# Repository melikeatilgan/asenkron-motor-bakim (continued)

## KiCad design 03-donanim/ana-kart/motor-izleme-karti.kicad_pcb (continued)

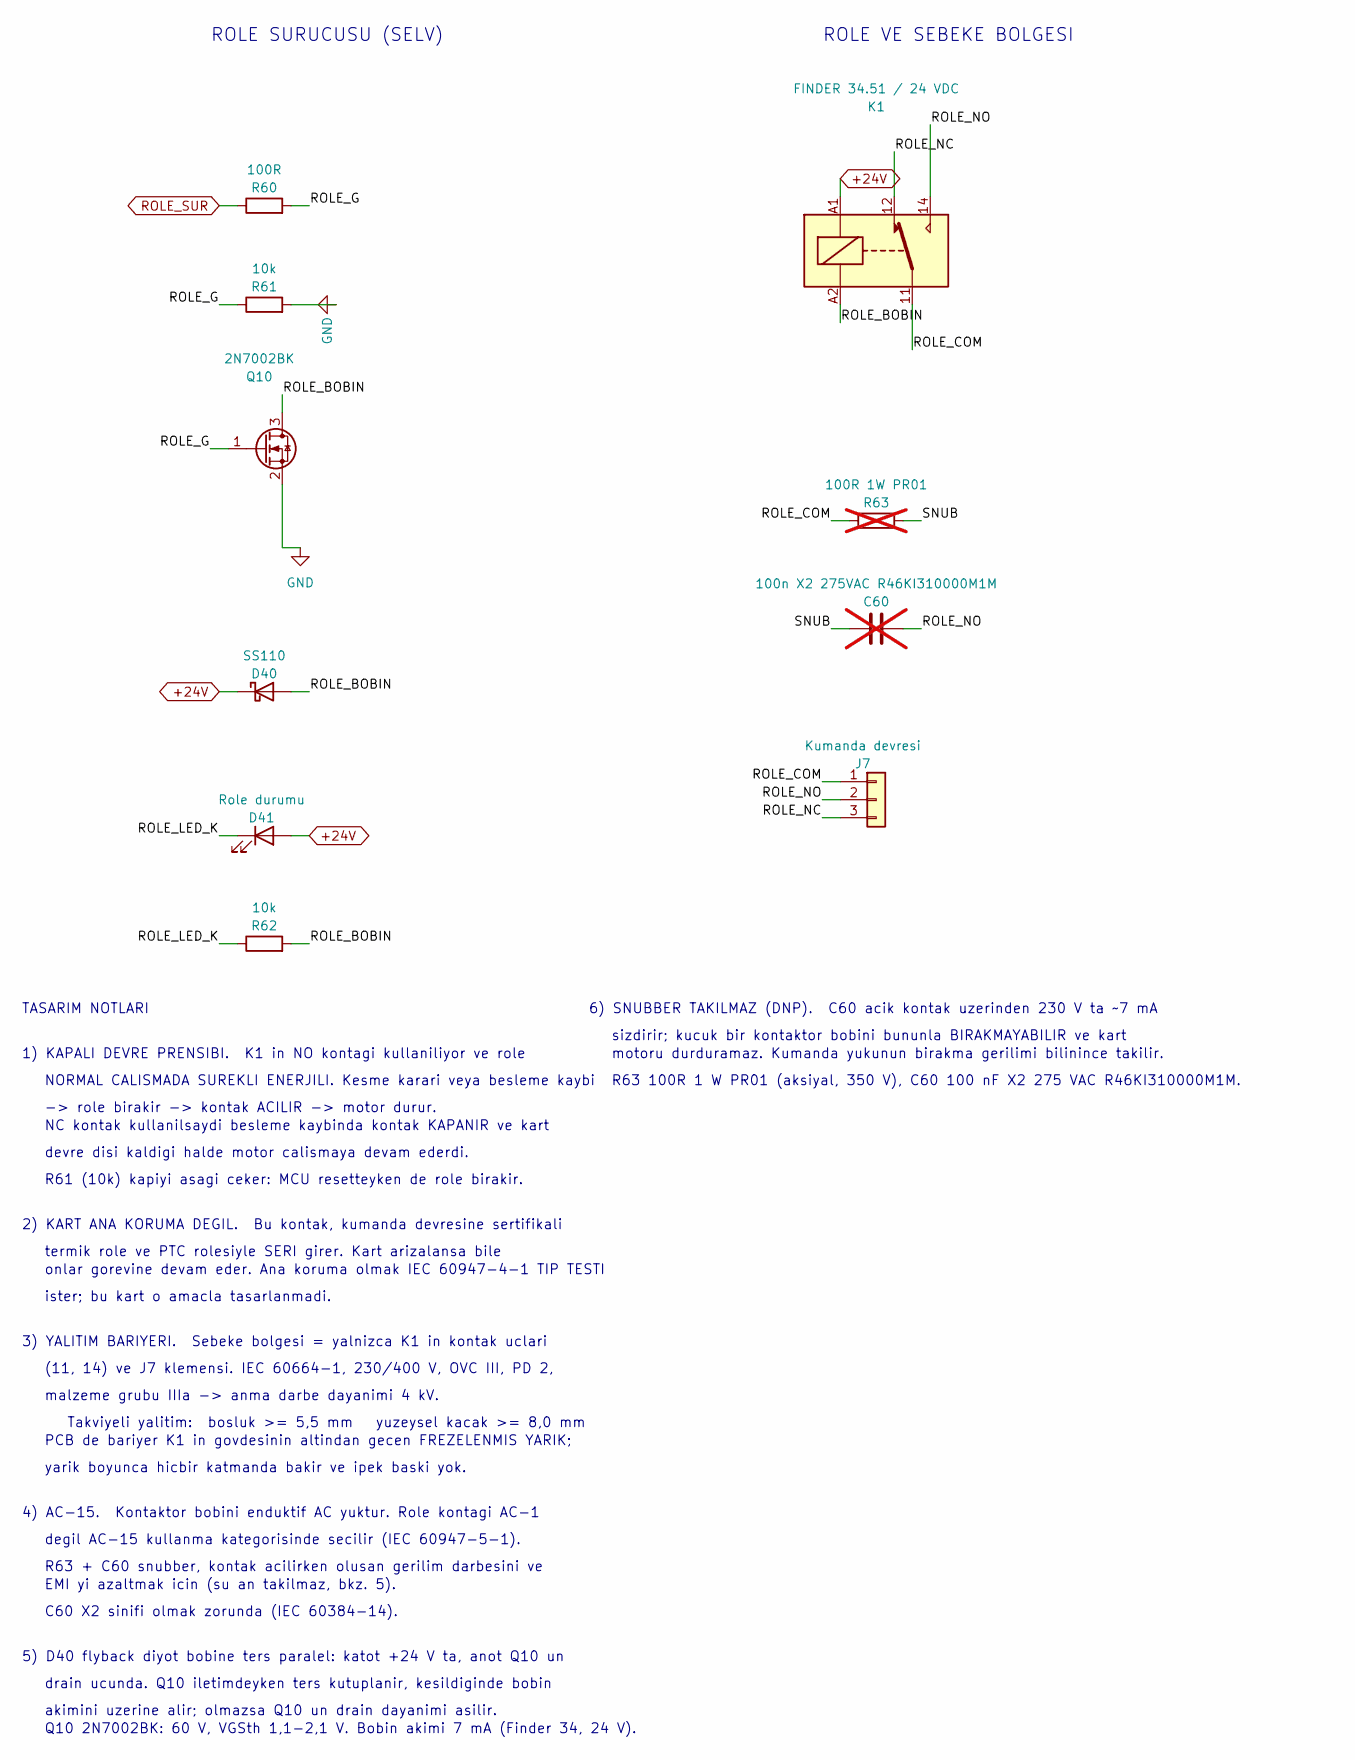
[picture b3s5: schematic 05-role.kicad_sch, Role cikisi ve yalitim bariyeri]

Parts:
C60: 100n X2 275VAC R46KI310000M1M; C_Rect_L18.0mm_W6.0mm_P15.00mm_FKS3_FKP3; not fitted
D40: SS110; D_SMA
D41: Role durumu; LED_0805_2012Metric
J7: Kumanda devresi; TerminalBlock_Phoenix_MKDS-1,5-3_1x03_P5.00mm_Horizontal
K1: FINDER 34.51 / 24 VDC; Relay_SPDT_Finder_34.51_Vertical_Fab
Q10: 2N7002BK; SOT-23
R60: 100R; R_0805_2012Metric
R61, R62: 10k; R_0805_2012Metric
R63: 100R 1W PR01; R_Axial_DIN0207_L6.3mm_D2.5mm_P10.16mm_Horizontal; not fitted

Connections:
+24V: D40.1 (K), D41.2 (A), K1.A1; also elsewhere on the board
/05-role/ROLE_BOBIN: D40.2 (A), K1.A2, Q10.3 (D), R62.2
/05-role/ROLE_COM: J7.1, K1.11, R63.1
/05-role/ROLE_G: Q10.1 (G), R60.2, R61.1
/05-role/ROLE_LED_K: D41.1 (K), R62.1
/05-role/ROLE_NC: J7.3, K1.12
/05-role/ROLE_NO: C60.2, J7.2, K1.14
/05-role/SNUB: C60.1, R63.2
GND: Q10.2 (S), R61.2; also elsewhere on the board
ROLE_SUR: R60.1; also elsewhere on the board

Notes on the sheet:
Q10 2N7002BK: 60 V, VGSth 1,1-2,1 V. Bobin akimi 7 mA (Finder 34, 24 V).
motoru durduramaz. Kumanda yukunun birakma gerilimi bilinince takilir.
Takviyeli yalitim: bosluk >= 5,5 mm yuzeysel kacak >= 8,0 mm
NORMAL CALISMADA SUREKLI ENERJILI. Kesme karari veya besleme kaybi
5) D40 flyback diyot bobine ters paralel: katot +24 V ta, anot Q10 un
devre disi kaldigi halde motor calismaya devam ederdi.
termik role ve PTC rolesiyle SERI girer. Kart arizalansa bile
6) SNUBBER TAKILMAZ (DNP). C60 acik kontak uzerinden 230 V ta ~7 mA
3) YALITIM BARIYERI. Sebeke bolgesi = yalnizca K1 in kontak uclari
degil AC-15 kullanma kategorisinde secilir (IEC 60947-5-1).
EMI yi azaltmak icin (su an takilmaz, bkz. 5).
1) KAPALI DEVRE PRENSIBI. K1 in NO kontagi kullaniliyor ve role
akimini uzerine alir; olmazsa Q10 un drain dayanimi asilir.
2) KART ANA KORUMA DEGIL. Bu kontak, kumanda devresine sertifikali
R61 (10k) kapiyi asagi ceker: MCU resetteyken de role birakir.
NC kontak kullanilsaydi besleme kaybinda kontak KAPANIR ve kart
onlar gorevine devam eder. Ana koruma olmak IEC 60947-4-1 TIP TESTI
ister; bu kart o amacla tasarlanmadi.
(11, 14) ve J7 klemensi. IEC 60664-1, 230/400 V, OVC III, PD 2,
R63 + C60 snubber, kontak acilirken olusan gerilim darbesini ve
yarik boyunca hicbir katmanda bakir ve ipek baski yok.
sizdirir; kucuk bir kontaktor bobini bununla BIRAKMAYABILIR ve kart
ROLE SURUCUSU (SELV)
TASARIM NOTLARI
R63 100R 1 W PR01 (aksiyal, 350 V), C60 100 nF X2 275 VAC R46KI310000M1M.
4) AC-15. Kontaktor bobini enduktif AC yuktur. Role kontagi AC-1
ROLE VE SEBEKE BOLGESI
drain ucunda. Q10 iletimdeyken ters kutuplanir, kesildiginde bobin
PCB de bariyer K1 in govdesinin altindan gecen FREZELENMIS YARIK;
malzeme grubu IIIa -> anma darbe dayanimi 4 kV.
-> role birakir -> kontak ACILIR -> motor durur.
C60 X2 sinifi olmak zorunda (IEC 60384-14).

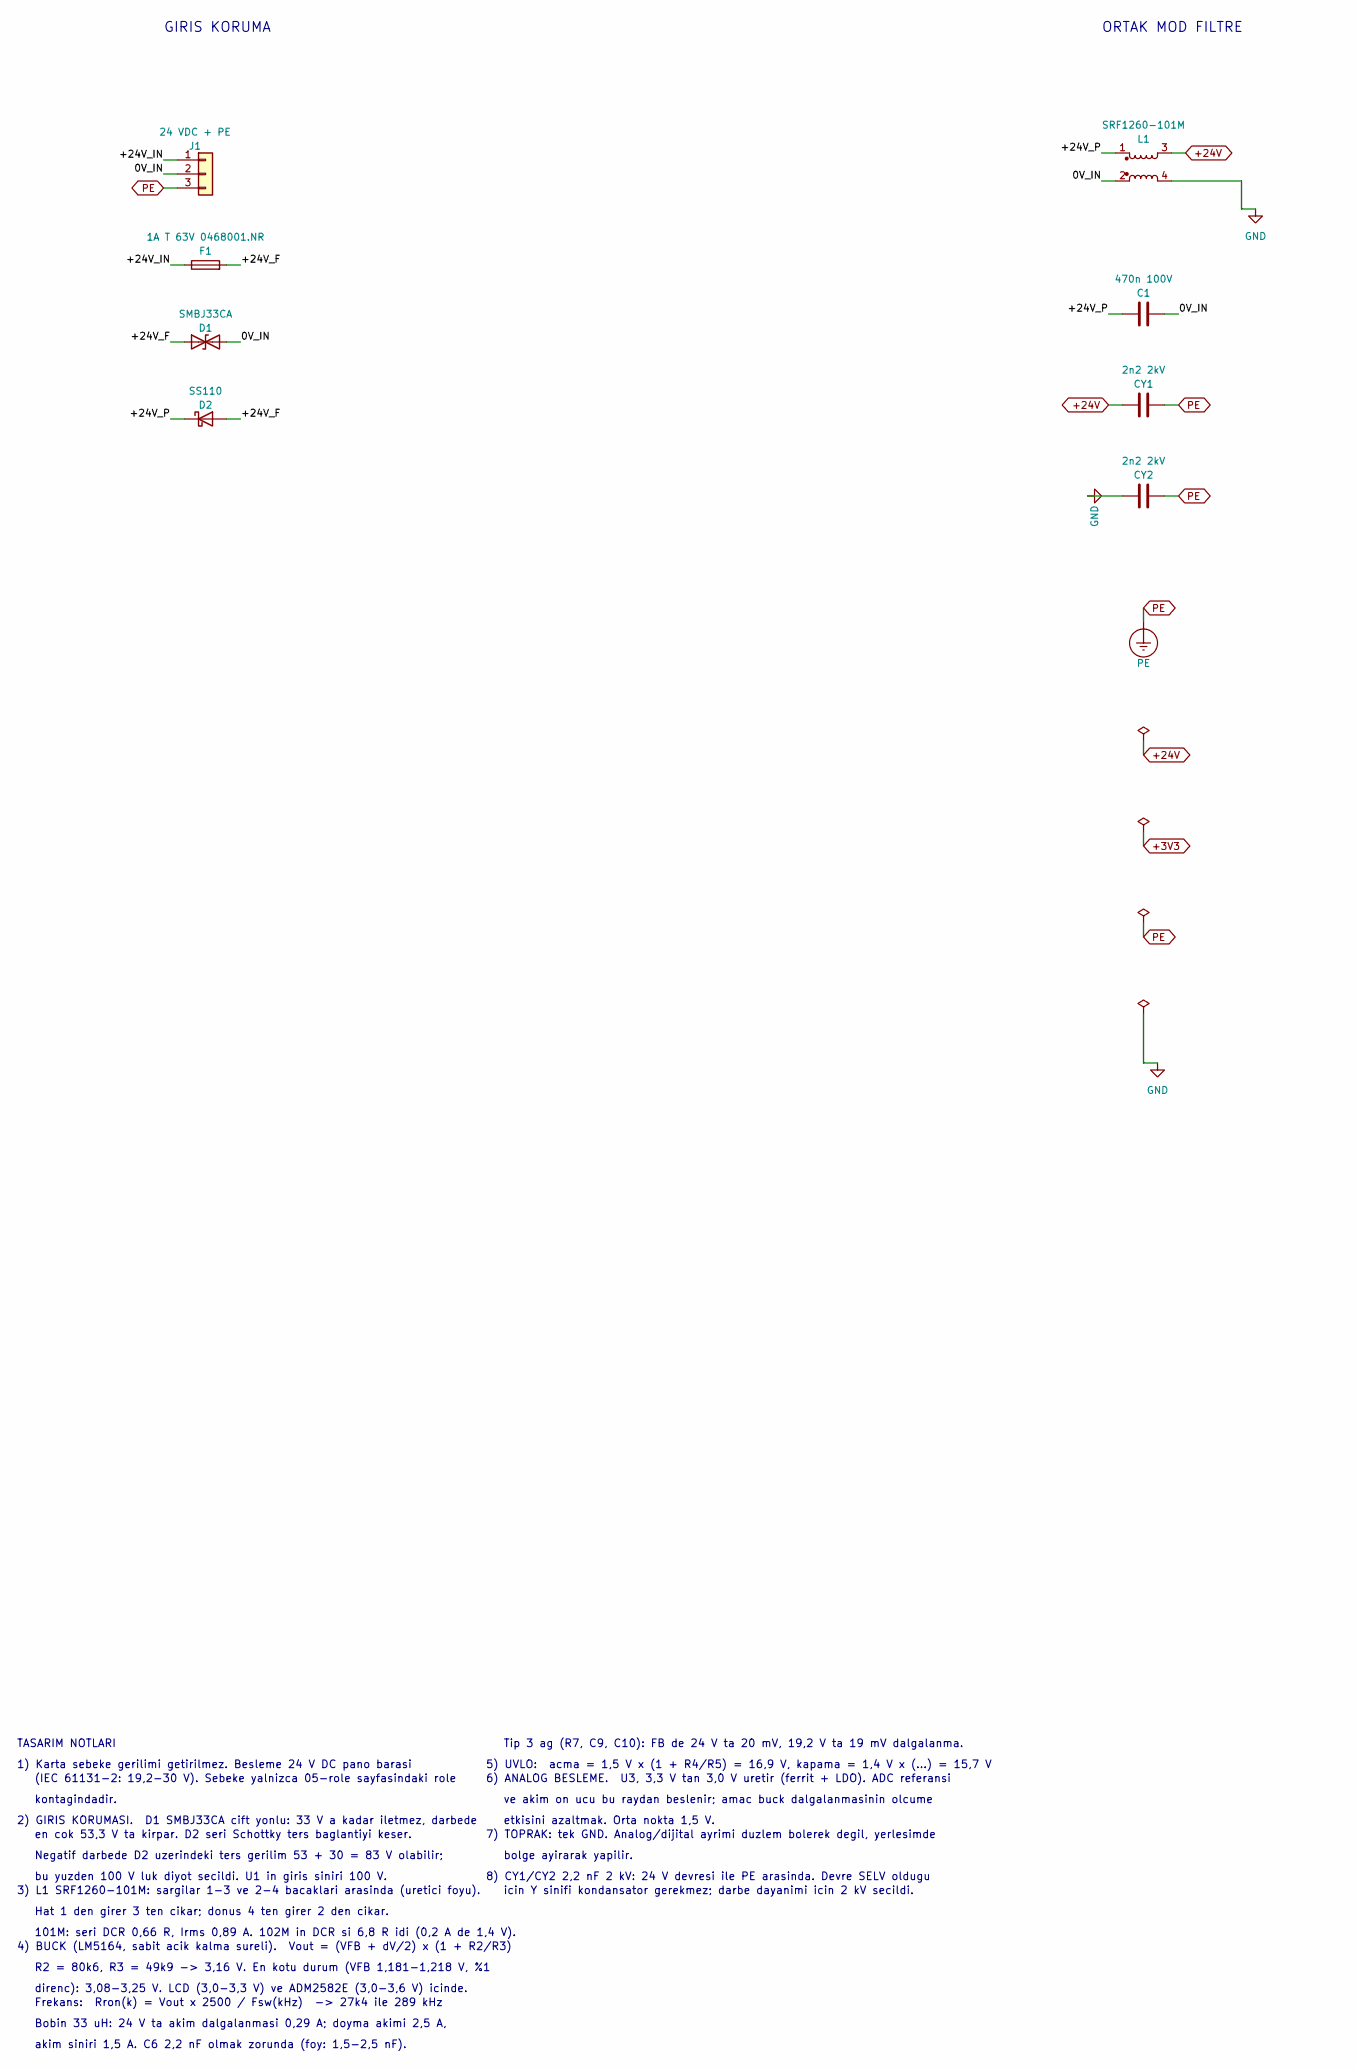
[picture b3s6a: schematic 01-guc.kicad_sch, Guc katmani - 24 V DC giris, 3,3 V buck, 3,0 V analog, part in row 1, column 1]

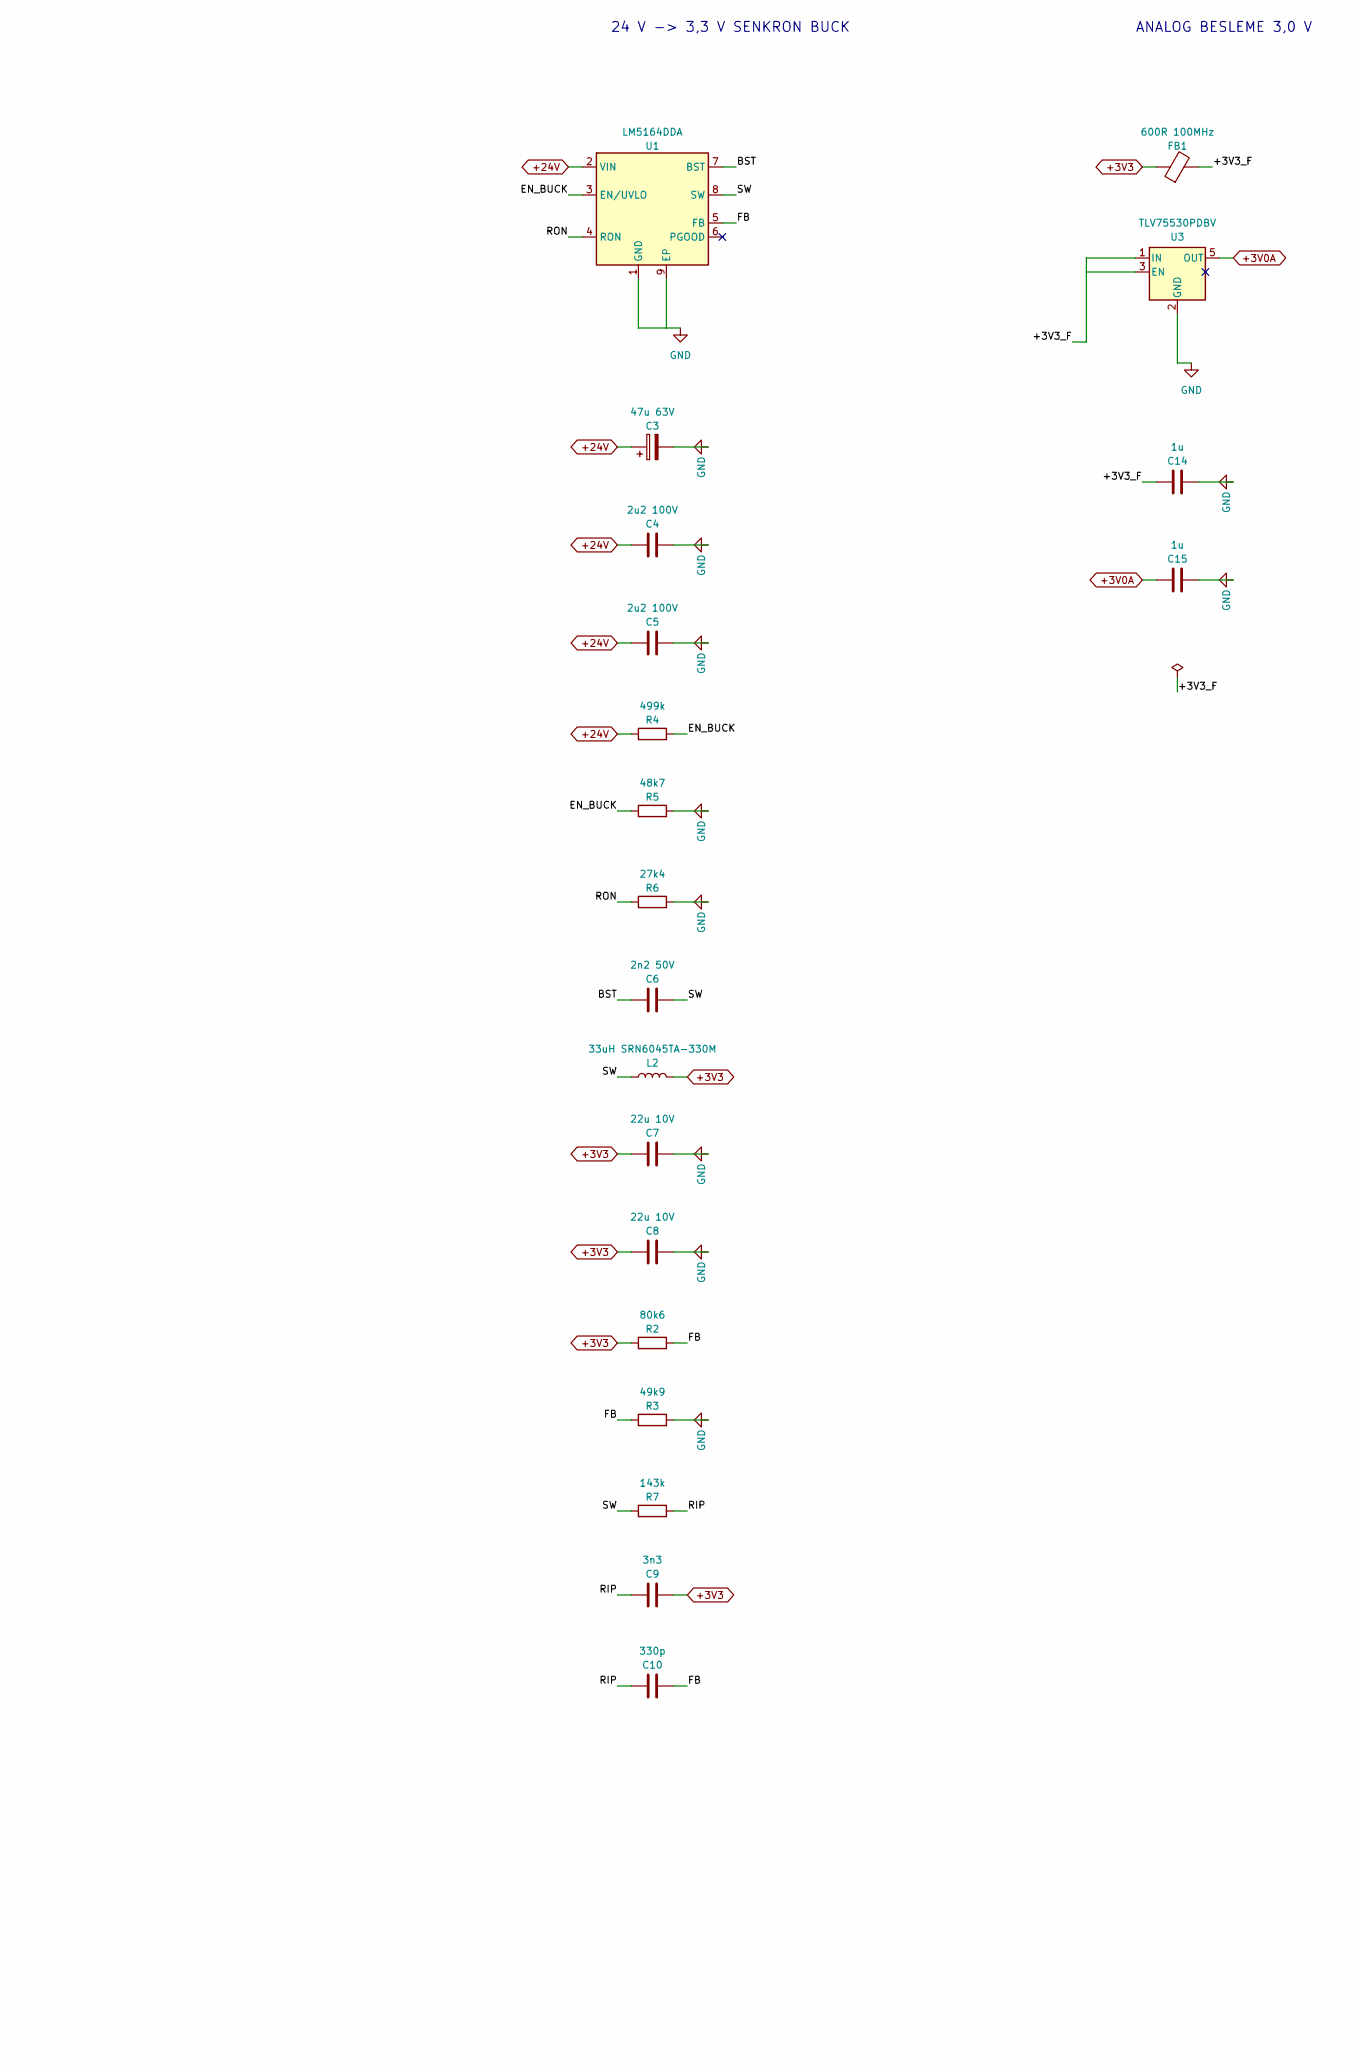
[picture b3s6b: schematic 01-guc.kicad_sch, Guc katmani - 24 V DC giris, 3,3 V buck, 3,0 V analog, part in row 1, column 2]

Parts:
C1: 470n 100V; C_1206_3216Metric
C3: 47u 63V; CP_Radial_D8.0mm_P3.50mm
C4, C5: 2u2 100V; C_1210_3225Metric
C6: 2n2 50V; C_0805_2012Metric
C7, C8: 22u 10V; C_1206_3216Metric
C9: 3n3; C_0805_2012Metric
C10: 330p; C_0805_2012Metric
C14, C15: 1u; C_0805_2012Metric
CY1, CY2: 2n2 2kV; C_1206_3216Metric
D1: SMBJ33CA; D_SMB
D2: SS110; D_SMA
F1: 1A T 63V 0468001.NR; Fuse_1206_3216Metric
FB1: 600R 100MHz; L_0805_2012Metric
J1: 24 VDC + PE; TerminalBlock_Phoenix_MKDS-1,5-3_1x03_P5.00mm_Horizontal
L1: SRF1260-101M; L_CommonModeChoke_Bourns_SRF1260
L2: 33uH SRN6045TA-330M; L_Bourns_SRN6045TA
R2: 80k6; R_0805_2012Metric
R3: 49k9; R_0805_2012Metric
R4: 499k; R_0805_2012Metric
R5: 48k7; R_0805_2012Metric
R6: 27k4; R_0805_2012Metric
R7: 143k; R_0805_2012Metric
U1: LM5164DDA; HSOP-8-1EP_3.9x4.9mm_P1.27mm_EP2.41x3.1mm_ThermalVias
U3: TLV75530PDBV; SOT-23-5

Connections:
+3V0A: C15.1, U3.5 (OUT); also elsewhere on the board
+3V3: C7.1, C8.1, C9.2, FB1.1, L2.2, R2.1; also elsewhere on the board
+24V: C3.1, C4.1, C5.1, CY1.1, L1.3, R4.1, U1.2 (VIN); also elsewhere on the board
/01-guc/0V_IN: C1.2, D1.2 (A2), J1.2, L1.2
/01-guc/+3V3_F: C14.1, FB1.2, U3.1 (IN), U3.3 (EN)
/01-guc/+24V_F: D1.1 (A1), D2.2 (A), F1.2
/01-guc/+24V_IN: F1.1, J1.1
/01-guc/+24V_P: C1.1, D2.1 (K), L1.1
/01-guc/BST: C6.1, U1.7 (BST)
/01-guc/EN_BUCK: R4.2, R5.1, U1.3 (EN/UVLO)
/01-guc/FB: C10.2, R2.2, R3.1, U1.5 (FB)
/01-guc/RIP: C9.1, C10.1, R7.2
/01-guc/RON: R6.1, U1.4 (RON)
/01-guc/SW: C6.2, L2.1, R7.1, U1.8 (SW)
GND: C3.2, C4.2, C5.2, C7.2, C8.2, C14.2, C15.2, CY2.1, L1.4, R3.2, R5.2, R6.2, U1.1 (GND), U1.9 (EP), U3.2 (GND); also elsewhere on the board
PE: CY1.2, CY2.2, J1.3

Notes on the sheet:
7) TOPRAK: tek GND. Analog/dijital ayrimi duzlem bolerek degil, yerlesimde
R2 = 80k6, R3 = 49k9 -> 3,16 V. En kotu durum (VFB 1,181-1,218 V, %1
ve akim on ucu bu raydan beslenir; amac buck dalgalanmasinin olcume
Tip 3 ag (R7, C9, C10): FB de 24 V ta 20 mV, 19,2 V ta 19 mV dalgalanma.
(IEC 61131-2: 19,2-30 V). Sebeke yalnizca 05-role sayfasindaki role
8) CY1/CY2 2,2 nF 2 kV: 24 V devresi ile PE arasinda. Devre SELV oldugu
en cok 53,3 V ta kirpar. D2 seri Schottky ters baglantiyi keser.
Frekans: Rron(k) = Vout x 2500 / Fsw(kHz) -> 27k4 ile 289 kHz
Negatif darbede D2 uzerindeki ters gerilim 53 + 30 = 83 V olabilir;
2) GIRIS KORUMASI. D1 SMBJ33CA cift yonlu: 33 V a kadar iletmez, darbede
GIRIS KORUMA
direnc): 3,08-3,25 V. LCD (3,0-3,3 V) ve ADM2582E (3,0-3,6 V) icinde.
5) UVLO: acma = 1,5 V x (1 + R4/R5) = 16,9 V, kapama = 1,4 V x (...) = 15,7 V
24 V -> 3,3 V SENKRON BUCK
bolge ayirarak yapilir.
bu yuzden 100 V luk diyot secildi. U1 in giris siniri 100 V.
TASARIM NOTLARI
1) Karta sebeke gerilimi getirilmez. Besleme 24 V DC pano barasi
akim siniri 1,5 A. C6 2,2 nF olmak zorunda (foy: 1,5-2,5 nF).
3) L1 SRF1260-101M: sargilar 1-3 ve 2-4 bacaklari arasinda (uretici foyu).
Bobin 33 uH: 24 V ta akim dalgalanmasi 0,29 A; doyma akimi 2,5 A,
Hat 1 den girer 3 ten cikar; donus 4 ten girer 2 den cikar.
kontagindadir.
icin Y sinifi kondansator gerekmez; darbe dayanimi icin 2 kV secildi.
101M: seri DCR 0,66 R, Irms 0,89 A. 102M in DCR si 6,8 R idi (0,2 A de 1,4 V).
6) ANALOG BESLEME. U3, 3,3 V tan 3,0 V uretir (ferrit + LDO). ADC referansi
ORTAK MOD FILTRE
etkisini azaltmak. Orta nokta 1,5 V.
ANALOG BESLEME 3,0 V
4) BUCK (LM5164, sabit acik kalma sureli). Vout = (VFB + dV/2) x (1 + R2/R3)

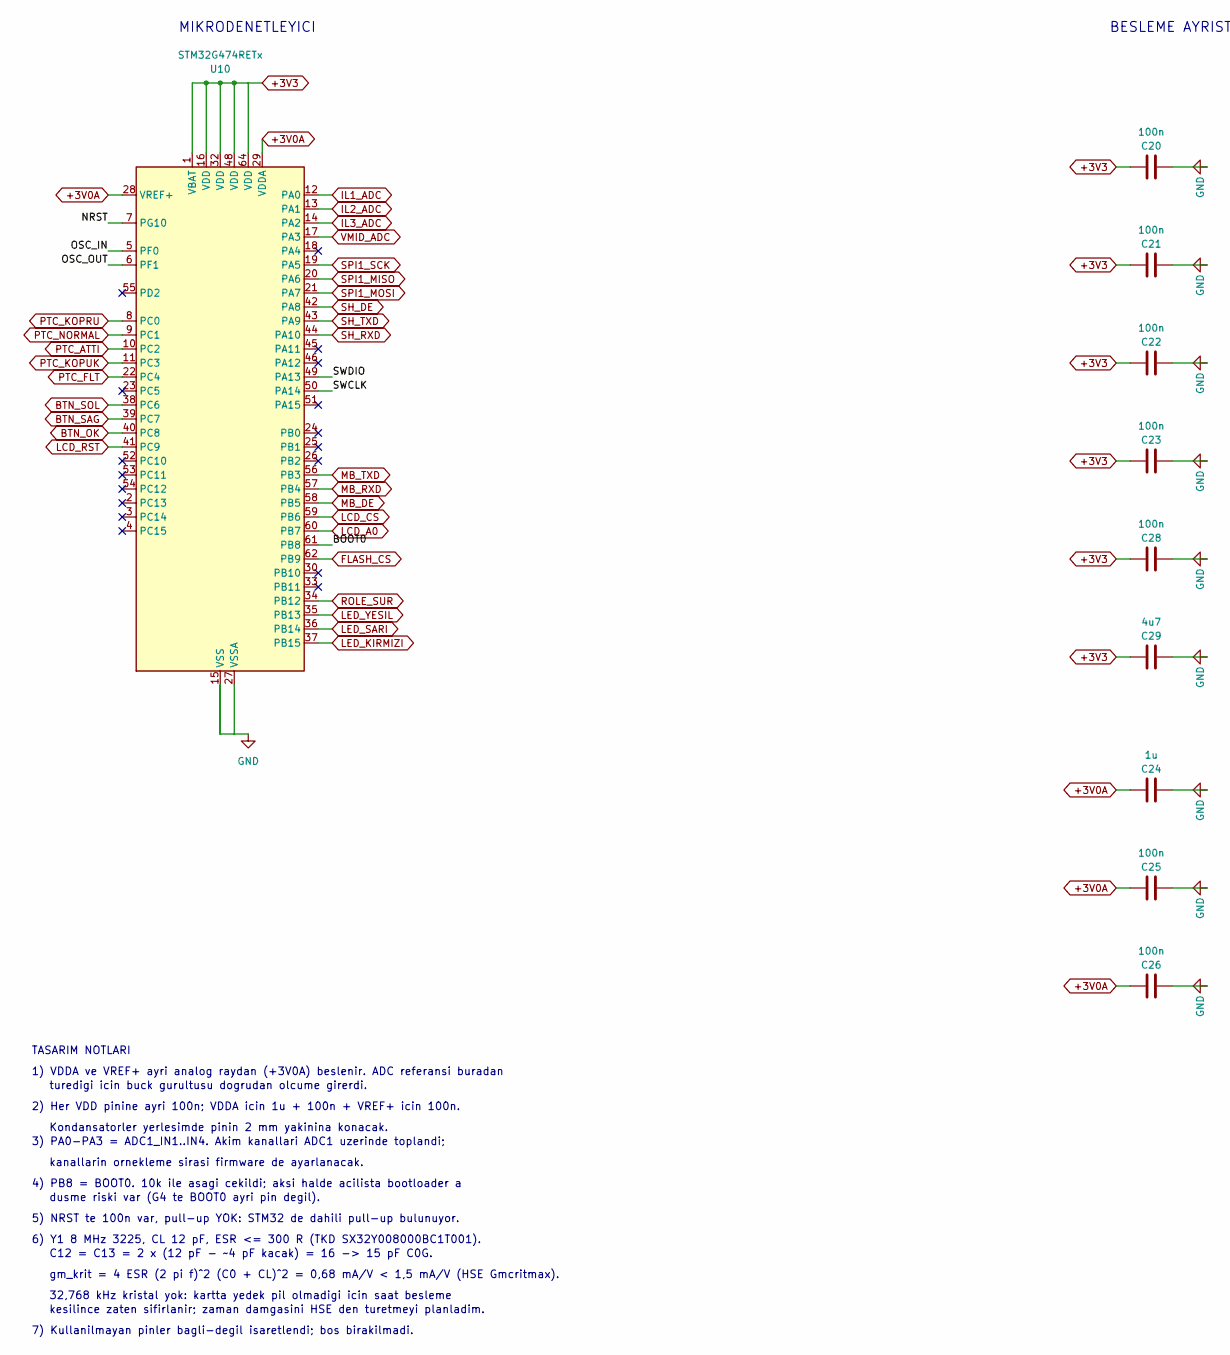
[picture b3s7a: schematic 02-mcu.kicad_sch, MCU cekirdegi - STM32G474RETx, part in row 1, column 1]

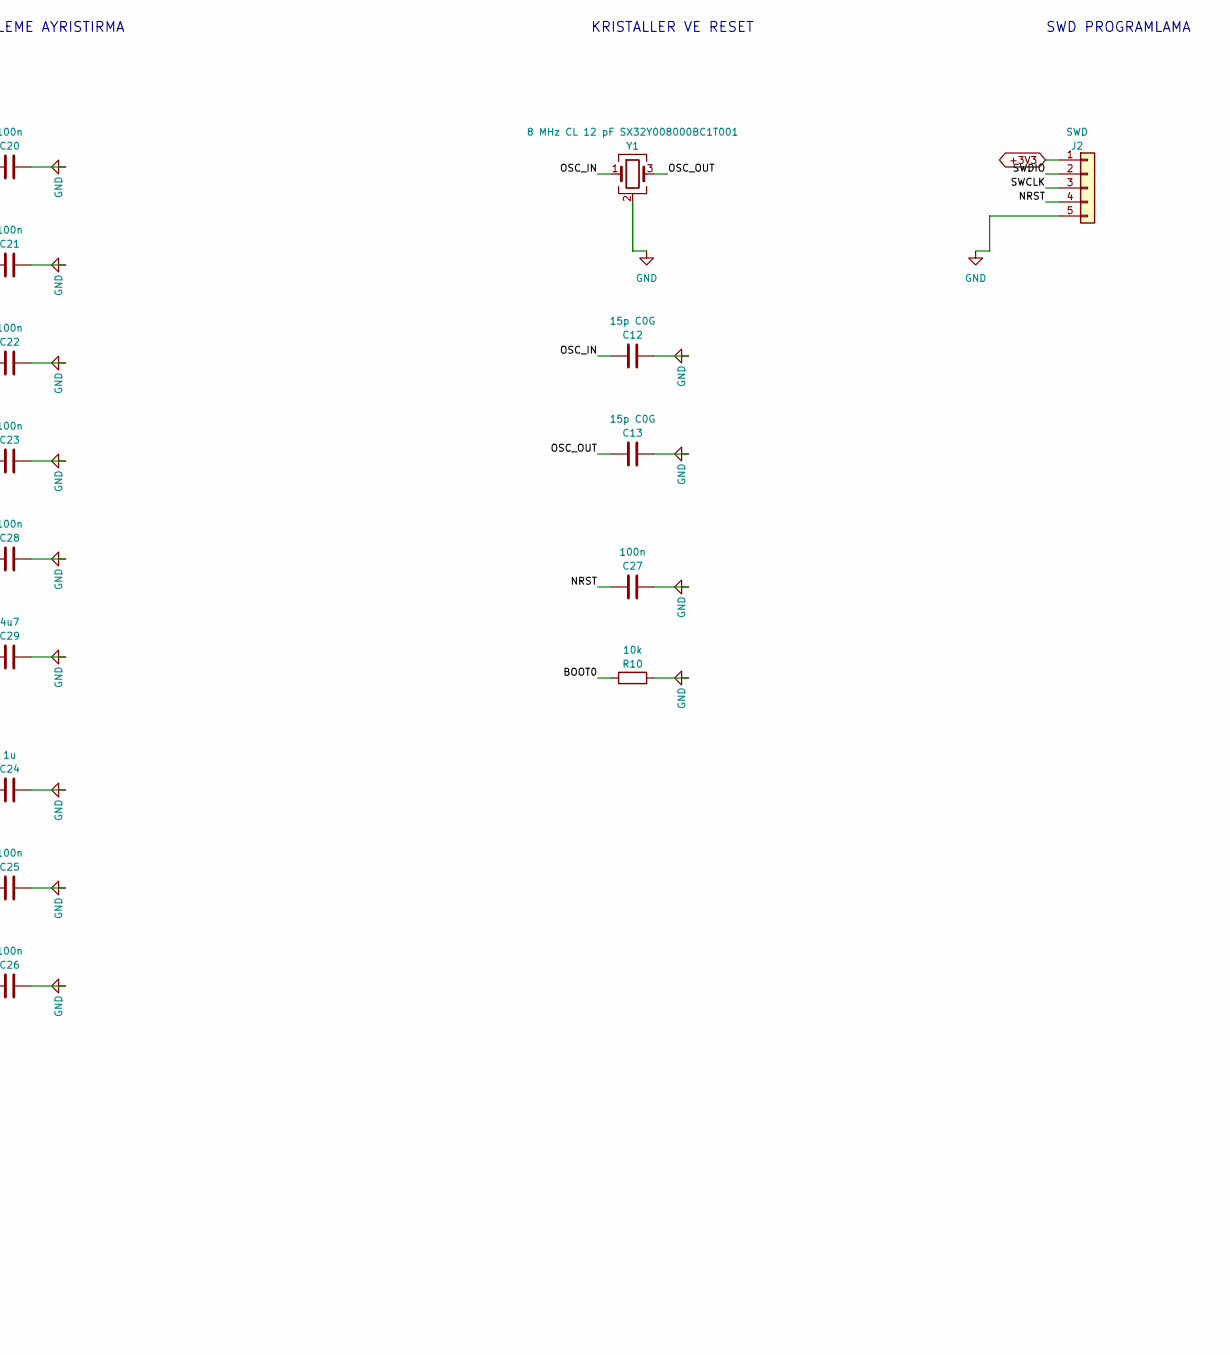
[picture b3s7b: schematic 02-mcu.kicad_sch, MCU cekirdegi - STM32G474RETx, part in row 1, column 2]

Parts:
C12, C13: 15p C0G; C_0805_2012Metric
C20, C21, C22, C23, C25, C26, C27, C28: 100n; C_0805_2012Metric
C24: 1u; C_0805_2012Metric
C29: 4u7; C_0805_2012Metric
J2: SWD; PinHeader_1x05_P2.54mm_Vertical
R10: 10k; R_0805_2012Metric
U10: STM32G474RETx; LQFP-64_10x10mm_P0.5mm
Y1: 8 MHz CL 12 pF SX32Y008000BC1T001; Crystal_SMD_3225-4Pin_3.2x2.5mm

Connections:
+3V0A: C24.1, C25.1, C26.1, U10.28 (VREF+), U10.29 (VDDA); also elsewhere on the board
+3V3: C20.1, C21.1, C22.1, C23.1, C28.1, C29.1, J2.1, U10.1 (VBAT), U10.16 (VDD), U10.32 (VDD), U10.48 (VDD), U10.64 (VDD); also elsewhere on the board
/02-mcu/BOOT0: R10.1, U10.61 (PB8)
/02-mcu/NRST: C27.1, J2.4, U10.7 (PG10)
/02-mcu/OSC_IN: C12.1, U10.5 (PF0), Y1.1
/02-mcu/OSC_OUT: C13.1, U10.6 (PF1), Y1.3
/02-mcu/SWCLK: J2.3, U10.50 (PA14)
/02-mcu/SWDIO: J2.2, U10.49 (PA13)
BTN_OK: U10.40 (PC8); also elsewhere on the board
BTN_SAG: U10.39 (PC7); also elsewhere on the board
BTN_SOL: U10.38 (PC6); also elsewhere on the board
FLASH_CS: U10.62 (PB9); also elsewhere on the board
GND: C12.2, C13.2, C20.2, C21.2, C22.2, C23.2, C24.2, C25.2, C26.2, C27.2, C28.2, C29.2, J2.5, R10.2, U10.15 (VSS), U10.27 (VSSA), U10.31 (VSS), U10.47 (VSS), U10.63 (VSS), Y1.2 (G), Y1.4 (G); also elsewhere on the board
IL1_ADC: U10.12 (PA0); also elsewhere on the board
IL2_ADC: U10.13 (PA1); also elsewhere on the board
IL3_ADC: U10.14 (PA2); also elsewhere on the board
LCD_A0: U10.60 (PB7); also elsewhere on the board
LCD_CS: U10.59 (PB6); also elsewhere on the board
LCD_RST: U10.41 (PC9); also elsewhere on the board
LED_KIRMIZI: U10.37 (PB15); also elsewhere on the board
LED_SARI: U10.36 (PB14); also elsewhere on the board
LED_YESIL: U10.35 (PB13); also elsewhere on the board
MB_DE: U10.58 (PB5); also elsewhere on the board
MB_RXD: U10.57 (PB4); also elsewhere on the board
MB_TXD: U10.56 (PB3); also elsewhere on the board
PTC_ATTI: U10.10 (PC2); also elsewhere on the board
PTC_FLT: U10.22 (PC4); also elsewhere on the board
PTC_KOPRU: U10.8 (PC0); also elsewhere on the board
PTC_KOPUK: U10.11 (PC3); also elsewhere on the board
PTC_NORMAL: U10.9 (PC1); also elsewhere on the board
ROLE_SUR: U10.34 (PB12); also elsewhere on the board
SH_DE: U10.42 (PA8); also elsewhere on the board
SH_RXD: U10.44 (PA10); also elsewhere on the board
SH_TXD: U10.43 (PA9); also elsewhere on the board
SPI1_MISO: U10.20 (PA6); also elsewhere on the board
SPI1_MOSI: U10.21 (PA7); also elsewhere on the board
SPI1_SCK: U10.19 (PA5); also elsewhere on the board
VMID_ADC: U10.17 (PA3); also elsewhere on the board

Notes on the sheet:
turedigi icin buck gurultusu dogrudan olcume girerdi.
KRISTALLER VE RESET
4) PB8 = BOOT0. 10k ile asagi cekildi; aksi halde acilista bootloader a
BESLEME AYRISTIRMA
C12 = C13 = 2 x (12 pF - ~4 pF kacak) = 16 -> 15 pF C0G.
1) VDDA ve VREF+ ayri analog raydan (+3V0A) beslenir. ADC referansi buradan
kanallarin ornekleme sirasi firmware de ayarlanacak.
kesilince zaten sifirlanir; zaman damgasini HSE den turetmeyi planladim.
7) Kullanilmayan pinler bagli-degil isaretlendi; bos birakilmadi.
MIKRODENETLEYICI
Kondansatorler yerlesimde pinin 2 mm yakinina konacak.
32,768 kHz kristal yok: kartta yedek pil olmadigi icin saat besleme
SWD PROGRAMLAMA
3) PA0-PA3 = ADC1_IN1..IN4. Akim kanallari ADC1 uzerinde toplandi;
5) NRST te 100n var, pull-up YOK: STM32 de dahili pull-up bulunuyor.
2) Her VDD pinine ayri 100n; VDDA icin 1u + 100n + VREF+ icin 100n.
6) Y1 8 MHz 3225, CL 12 pF, ESR <= 300 R (TKD SX32Y008000BC1T001).
gm_krit = 4 ESR (2 pi f)^2 (C0 + CL)^2 = 0,68 mA/V < 1,5 mA/V (HSE Gmcritmax).
TASARIM NOTLARI
dusme riski var (G4 te BOOT0 ayri pin degil).
